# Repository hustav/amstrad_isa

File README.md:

# Amstrad PPC 512/640 — ISA Expansion Board

An open-hardware **KiCad 8** design for an external-mount, internally-powered
**3-slot XT-class (8-bit) ISA expansion board** for the Amstrad PPC 512 and
PPC 640 portable PCs.

The PPC is the 1988-era Amstrad luggable that ships with a CMOS-level
expansion connector (DB25 + DB37) on its back. Amstrad sold an external
"Expansion Box" that was meant to *power* the PPC and add peripheral slots.
This project inverts the original topology: it **takes power from the PPC's
own PSU** and gives you three standard XT 8-bit ISA slots in a compact board
that clips onto the back of the machine via the two DB connectors — ready to
host modern flash-based peripherals (XT-IDE, floppy emulators, network
cards, etc.).

## Gallery

The board has been fabricated and tested in a real Amstrad PPC 640 —
booting DOS from a CompactFlash card via an XT-IDE controller. Photos
below are of the assembled board in service.

| | |
|---|---|
|  |  |
| Board mated to the PPC's DB25 + DB37 expansion port. | Top-down view showing the three ISA slots fanning out the back. |
|  |  |
| XT-IDE card with CompactFlash plugged into the centre slot. | The PPC 640 booting and running Test Drive from the CF card. |

## Repository layout

```
amstrad_isa/
├── README.md                  — this file
├── LICENSE                    — MIT
├── .gitignore                 — KiCad / Python / OS cruft
├── kicad/
│   ├── ppc-isa-expansion.kicad_pro
│   ├── ppc-isa-expansion.kicad_sch
│   ├── ppc-isa-expansion.kicad_pcb
│   ├── sym-lib-table          — project-local symbol libraries
│   ├── fp-lib-table           — project-local footprint libraries
│   └── ppc-isa.pretty/        — custom ISA 8-bit slot footprint
├── scripts/
│   ├── generate_schematic.py  — regenerates the schematic from tables
│   ├── generate_pcb.py        — regenerates the PCB skeleton
│   └── generate_bom.py        — emits docs/BOM.csv
├── fab/                       — ready-to-order gerbers + JLCPCB zip
├── docs/
│   ├── design_notes.md        — the *why* behind the schematic choices
│   ├── BOM.csv                — bill of materials
│   └── Amstrad_PPC_Technical_Reference_Manual.pdf
└── photos/                    — build & in-machine reference shots
```

## I just want a board — no KiCad

If you don't want to install KiCad, the [`fab/`](fab/) folder contains a
ready-to-order gerber set straight from the committed `.kicad_pcb`.

1. Download [`fab/ppc-isa-expansion-gerbers.zip`](fab/ppc-isa-expansion-gerbers.zip)
   (no need to extract it).
2. Go to your favourite board house — **JLCPCB**, **PCBWay**, **OSH Park**
   and **Aisler** all accept this format unchanged.
3. Upload the zip. The defaults are fine: 2 layers, 1.6 mm FR-4, HASL or
   ENIG finish, any colour. Quantity 5 is usually the minimum and runs
   ~$5 + shipping.
4. Order, wait, populate from [`docs/BOM.csv`](docs/BOM.csv).

The gerbers in `fab/` always match the committed `.kicad_pcb`. If you fork
and re-route, re-plot from KiCad and replace the contents of `fab/`.

## Build from source (with KiCad)

```bash
git clone git@github.com:hustav/amstrad_isa.git
cd amstrad_isa

# Optional: regenerate the schematic / PCB from the Python source of truth
python3 scripts/generate_schematic.py
python3 scripts/generate_pcb.py

# Open the project
kicad kicad/ppc-isa-expansion.kicad_pro
```

The `.kicad_sch` and `.kicad_pcb` files were initially **generated** by the
scripts in `scripts/` — those scripts remain the source of truth for the
netlist. The current `.kicad_pcb` has been routed by hand on top of that
skeleton, so re-running `generate_pcb.py` would overwrite the routing.
If you need to change the netlist, regenerate the skeleton and then redo
the affected traces.

## Key design choices

| Area | Choice | Reason |
| --- | --- | --- |
| Form factor | External-mount, ~120 × 99 mm | Clips onto the PPC's DB25 + DB37 expansion port |
| Slots | 3 × XT 8-bit ISA (62-pin) | Standard pinout, matches prior-art boards |
| Power source | Drawn from the PPC's internal PSU via the expansion cable | No external brick required |
| −5 V rail | Taken directly from connector B pin 17 | Tech Ref §1.18 confirms PPC sources −5 V |
| Component style | SMD only — SOIC, 0805, SIP network | Hand-solderable with a fine-tip iron |
| Buffering | 2 × 74HC244 for A00..A07 + 8 control signals | Drives the loaded capacitance of 3 ISA slots |
| Data bus | Unbuffered, 10 kΩ pull-ups via RR1 | Per Amstrad Tech Ref CMOS-to-TTL note |
| Activity LED | Removed (BEAT flip-flop omitted) | Purely cosmetic; saves 1× SOIC-14 + RC bits |

Full rationale lives in [docs/design_notes.md](docs/design_notes.md).

## Power topology — important caveat

The Amstrad PPC Technical Reference Manual (§1.18) states that the original
Expansion Box is intended to *supply* power **to** the PPC, not draw from
it. Connector B pin 20 is an **EXT PWR input** to the PPC's regulator.

This design **reverses that flow** — all four rails (+5 V, +12 V, −5 V,
−12 V) are *drawn* from the PPC's expansion connector:

- +5 V from connector A pin 1 and connector B pin 37
- +12 V from connector B pin 36
- −5 V from connector B pin 17
- −12 V from connector B pin 18

Pin 20 (EXT PWR into the PPC) is **left floating** — voltage is never
injected back into the PPC.

**Safe for modern peripherals.** An original floppy or 10 MB Winchester drew
5–10 W. A flash-based XT-IDE with a CF card draws ~100–200 mA on +5 V
(0.5–1 W). Three flash peripherals are comfortably within the headroom the
original PSU left for the Expansion Box port.

**Not safe for original drives.** If you try to use the original floppy or
HDD controllers through this board, the PPC's PSU may brown out. In that
case, build an externally-powered (ATX) variant instead.

## Amstrad expansion pinout (Tech Ref §1.18)

### Connector A (DB25 male on the board)

Mostly the address bus.

| Pin | Signal | Notes |
| --- | --- | --- |
| 1 | +5 V | **power input** |
| 2 | TC | DMA terminal-count |
| 3, 16, 4, 17, 5, 18, 6, 19, 7, 20, 8, 21 | A19..A08 | Unbuffered |
| 9, 22, 10, 23, 11, 24, 12, 25 | A07b..A00b | Buffered on PPC side; re-buffered by U2 |
| 13 | AEN | Address enable |
| 14 | GND | |
| 15 | DACK0 | |

### Connector B (DB37 male on the board)

Data bus, IRQs, DMA, control signals, power.

| Pin | Signal | Notes |
| --- | --- | --- |
| 1 | −20 V | **unused, left NC** |
| 2–4, 21–23 | IRQ2..IRQ7 | Pass-through |
| 5 | I/O RDY | Pass-through |
| 6, 24–25 | DACK1..DACK3 | Pass-through |
| 7 | I/O CHCK | Pass-through |
| 8, 26–27 | DRQ1..DRQ3 | Pass-through |
| 9 | OSC(b) | 14.318 MHz buffered on PPC side; re-buffered by U1 |
| 10–12, 28–31 | MEMR(b), IOR(b), ALE(b), MEMW(b), IOW(b), RESET(b), CK4(b) | Re-buffered by U1 |
| 13–16, 32–35 | D7..D0 | Unbuffered; 10 kΩ pull-ups via RR1 |
| 17 | −5 V | **power input** |
| 18 | −12 V | **power input** |
| 19 | GND | |
| 20 | EXT PWR | **NOT USED** — would feed the PPC's regulator |
| 36 | +12 V | **power input** |
| 37 | +5 V | **power input** |

The full Amstrad PPC Technical Reference Manual is included in
[docs/](docs/Amstrad_PPC_Technical_Reference_Manual.pdf) for reference.

## Credits and prior art

This design builds on two community projects, both of which are
externally-mounted boards that hang off the PPC's DB25 + DB37 connectors:

- **João (enide.net)** — original internally-powered design. Provided the
  mechanical approach and power topology. Only the gerbers were available
  (the project is currently offline), so the schematic was reverse-
  engineered from those files and cross-referenced against the
  Retrotheory design below.
- **Retrotheory — [amstradppc_expansion](https://github.com/retrotheory/amstradppc_expansion)** —
  ATX-powered variant. Provided the full schematic used as the electrical
  reference (74HC244 pinouts, the BEAT LED divider using a 74HC74, etc.).

Many thanks to both for sharing their work — without them this design
would not exist.

## License

Released under the **MIT License**. See [LICENSE](LICENSE).

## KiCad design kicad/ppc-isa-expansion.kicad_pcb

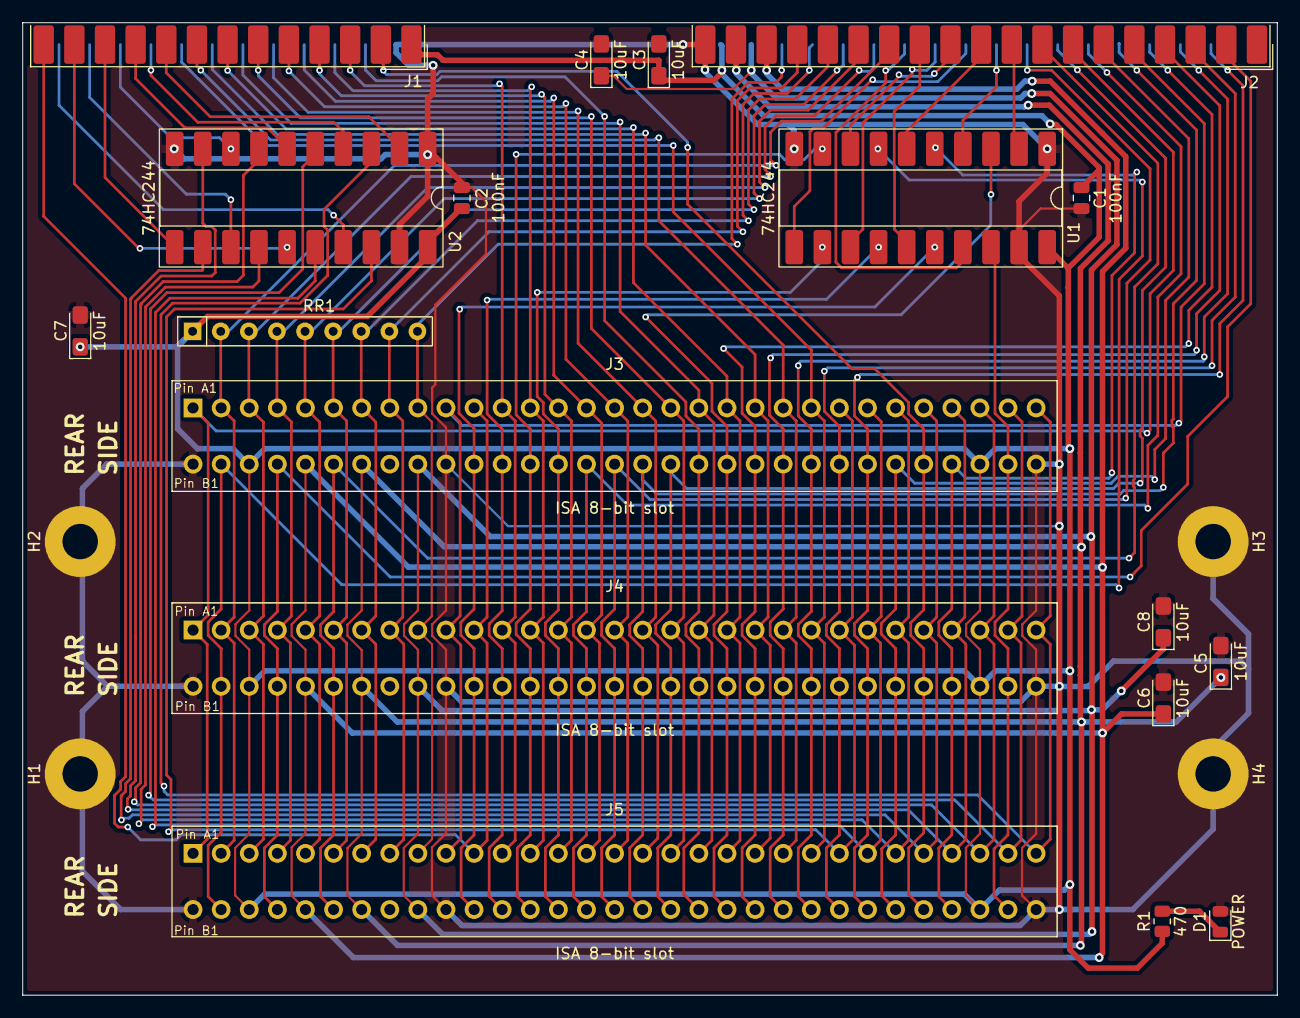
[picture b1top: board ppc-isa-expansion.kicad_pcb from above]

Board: 2 copper layers, 113.4 x 87.9 mm, 22 parts (0 on the bottom side), 75 nets.

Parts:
C1, C2: 100nF; C_0805_2012Metric
C3, C4, C5, C6, C7, C8: 10uF; CP_EIA-3216-12_Kemet-S_HandSolder
D1: POWER; LED_0805_2012Metric
H1, H2, H3, H4: MountingHole_M3; MountingHole_3.2mm_M3_Pad
J1: DB25 Male; DSUB-25_Pins_EdgeMount_P2.77mm
J2: DB37 Male; DSUB-37_Pins_EdgeMount_P2.77mm
J3, J4, J5: ISA 8-bit slot; ISA_8Bit_Slot
R1: 470; R_0805_2012Metric
RR1: 10k; R_Array_SIP9
U1, U2: 74HC244; DIP-20_W8.89mm_SMDSocket_LongPads

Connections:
+5V: C1.1, C2.1, C3.1, C7.1, J1.1 (+5V), J2.37 (+5V), J3.34 (+5V), J3.60 (+5V), J4.34 (+5V), J4.60 (+5V), J5.34 (+5V), J5.60 (+5V), R1.1, RR1.1 (COM), U1.20 (VCC), U2.20 (VCC)
+12V: C4.1, C8.1, J2.36 (+12V), J3.40 (+12V), J4.40 (+12V), J5.40 (+12V)
-5V: C6.1, J2.17 (-5V), J3.36 (-5V), J4.36 (-5V), J5.36 (-5V)
-12V: C5.1, J2.18 (-12V), J3.38 (-12V), J4.38 (-12V), J5.38 (-12V)
A00: J3.31 (A00), J4.31 (A00), J5.31 (A00), U2.3 (2Y3)
A00b: J1.25 (A00b), U2.17 (2A3)
A01: J3.30 (A01), J4.30 (A01), J5.30 (A01), U2.5 (2Y2)
A01b: J1.12 (A01b), U2.15 (2A2)
A02: J3.29 (A02), J4.29 (A02), J5.29 (A02), U2.7 (2Y1)
A02b: J1.24 (A02b), U2.13 (2A1)
A03: J3.28 (A03), J4.28 (A03), J5.28 (A03), U2.9 (2Y0)
A03b: J1.11 (A03b), U2.11 (2A0)
A04: J3.27 (A04), J4.27 (A04), J5.27 (A04), U2.12 (1Y3)
A04b: J1.23 (A04b), U2.8 (1A3)
A05: J3.26 (A05), J4.26 (A05), J5.26 (A05), U2.14 (1Y2)
A05b: J1.10 (A05b), U2.6 (1A2)
A06: J3.25 (A06), J4.25 (A06), J5.25 (A06), U2.16 (1Y1)
A06b: J1.22 (A06b), U2.4 (1A1)
A07: J3.24 (A07), J4.24 (A07), J5.24 (A07), U2.18 (1Y0)
A07b: J1.9 (A07b), U2.2 (1A0)
A08: J1.21 (A08), J3.23 (A08), J4.23 (A08), J5.23 (A08)
A09: J1.8 (A09), J3.22 (A09), J4.22 (A09), J5.22 (A09)
A10: J1.20 (A10), J3.21 (A10), J4.21 (A10), J5.21 (A10)
A11: J1.7 (A11), J3.20 (A11), J4.20 (A11), J5.20 (A11)
A12: J1.19 (A12), J3.19 (A12), J4.19 (A12), J5.19 (A12)
A13: J1.6 (A13), J3.18 (A13), J4.18 (A13), J5.18 (A13)
A14: J1.18 (A14), J3.17 (A14), J4.17 (A14), J5.17 (A14)
A15: J1.5 (A15), J3.16 (A15), J4.16 (A15), J5.16 (A15)
A16: J1.17 (A16), J3.15 (A16), J4.15 (A16), J5.15 (A16)
A17: J1.4 (A17), J3.14 (A17), J4.14 (A17), J5.14 (A17)
A18: J1.16 (A18), J3.13 (A18), J4.13 (A18), J5.13 (A18)
A19: J1.3 (A19), J3.12 (A19), J4.12 (A19), J5.12 (A19)
AEN: J1.13 (AEN), J3.11 (AEN), J4.11 (AEN), J5.11 (AEN)
ALE: J3.59 (ALE), J4.59 (ALE), J5.59 (ALE), U1.5 (2Y2)
ALEb: J2.12 (ALEb), U1.15 (2A2)
CK4b: J2.31 (CK4b), U1.17 (2A3)
CLK: J3.51 (CLK), J4.51 (CLK), J5.51 (CLK), U1.3 (2Y3)
D0: J2.35 (D0), J3.9 (D0), J4.9 (D0), J5.9 (D0), RR1.9 (R8)
D1: J2.16 (D1), J3.8 (D1), J4.8 (D1), J5.8 (D1), RR1.8 (R7)
D2: J2.34 (D2), J3.7 (D2), J4.7 (D2), J5.7 (D2), RR1.7 (R6)
D3: J2.15 (D3), J3.6 (D3), J4.6 (D3), J5.6 (D3), RR1.6 (R5)
D4: J2.33 (D4), J3.5 (D4), J4.5 (D4), J5.5 (D4), RR1.5 (R4)
D5: J2.14 (D5), J3.4 (D5), J4.4 (D5), J5.4 (D5), RR1.4 (R3)
D6: J2.32 (D6), J3.3 (D6), J4.3 (D6), J5.3 (D6), RR1.3 (R2)
D7: J2.13 (D7), J3.2 (D7), J4.2 (D7), J5.2 (D7), RR1.2 (R1)
DRQ1: J2.26 (DRQ1), J3.49 (DRQ1), J4.49 (DRQ1), J5.49 (DRQ1)
DRQ2: J2.8 (DRQ2), J3.37 (DRQ2), J4.37 (DRQ2), J5.37 (DRQ2)
DRQ3: J2.27 (DRQ3), J3.47 (DRQ3), J4.47 (DRQ3), J5.47 (DRQ3)
GND: C1.2, C2.2, C3.2, C4.2, C5.2, C6.2, C7.2, C8.2, D1.2 (A), H1.1, H2.1, H3.1, H4.1, J1.14 (GND), J2.19 (GND), J3.32 (GND), J3.41 (GND), J3.62 (GND), J4.32 (GND), J4.41 (GND), J4.62 (GND), J5.32 (GND), J5.41 (GND), J5.62 (GND), U1.1 (~1OE), U1.10 (GND), U1.19 (~2OE), U2.1 (~1OE), U2.10 (GND), U2.19 (~2OE)
IO_RDY: J2.5 (IO_RDY), J3.10 (IO_RDY), J4.10 (IO_RDY), J5.10 (IO_RDY)
IRQ2: J2.2 (IRQ2), J3.35 (IRQ2), J4.35 (IRQ2), J5.35 (IRQ2)
IRQ3: J2.21 (IRQ3), J3.56 (IRQ3), J4.56 (IRQ3), J5.56 (IRQ3)
IRQ4: J2.3 (IRQ4), J3.55 (IRQ4), J4.55 (IRQ4), J5.55 (IRQ4)
IRQ5: J2.22 (IRQ5), J3.54 (IRQ5), J4.54 (IRQ5), J5.54 (IRQ5)
IRQ6: J2.4 (IRQ6), J3.53 (IRQ6), J4.53 (IRQ6), J5.53 (IRQ6)
IRQ7: J2.23 (IRQ7), J3.52 (IRQ7), J4.52 (IRQ7), J5.52 (IRQ7)
unnamed: D1.1 (K), R1.2
OSC: J3.61 (OSC), J4.61 (OSC), J5.61 (OSC), U1.18 (1Y0)
OSCb: J2.9 (OSCb), U1.2 (1A0)
RESET: J3.33 (RESET), J4.33 (RESET), J5.33 (RESET), U1.7 (2Y1)
RESETb: J2.30 (RESETb), U1.13 (2A1)
TC: J1.2 (TC), J3.58 (TC), J4.58 (TC), J5.58 (TC)
~DACK0: J1.15 (~DACK0), J3.50 (~DACK0), J4.50 (~DACK0), J5.50 (~DACK0)
~DACK1: J2.24 (~DACK1), J3.48 (~DACK1), J4.48 (~DACK1), J5.48 (~DACK1)
~DACK2: J2.6 (~DACK2), J3.57 (~DACK2), J4.57 (~DACK2), J5.57 (~DACK2)
~DACK3: J2.25 (~DACK3), J3.46 (~DACK3), J4.46 (~DACK3), J5.46 (~DACK3)
~IOCHCK: J2.7 (~IOCHCK), J3.1 (~IOCHCK), J4.1 (~IOCHCK), J5.1 (~IOCHCK)
~IOR: J3.45 (~IOR), J4.45 (~IOR), J5.45 (~IOR), U1.12 (1Y3)
~IORb: J2.11 (~IORb), U1.8 (1A3)
~IOW: J3.44 (~IOW), J4.44 (~IOW), J5.44 (~IOW), U1.9 (2Y0)
~IOWb: J2.29 (~IOWb), U1.11 (2A0)
~MEMRb: J2.10 (~MEMRb), U1.6 (1A2)
~MEMWb: J2.28 (~MEMWb), U1.4 (1A1)
~SMEMR: J3.43 (~SMEMR), J4.43 (~SMEMR), J5.43 (~SMEMR), U1.14 (1Y2)
~SMEMW: J3.42 (~SMEMW), J4.42 (~SMEMW), J5.42 (~SMEMW), U1.16 (1Y1)

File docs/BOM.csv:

References,Quantity,Value,Footprint,Description,Notes
"U1, U2",2,74HC244,Package_SO:SOIC-20W_7.5x12.8mm_P1.27mm,"Octal bus buffer / line driver, non-inverting",SOIC-20 wide body; any 74HC244 or 74HCT244 works
"C1, C2, C3, C4, C5",5,100nF,Capacitor_SMD:C_0805_2012Metric,"Chip capacitor, X7R ceramic",0805; 50V rating
"C6, C7, C8, C9",4,10uF,Capacitor_SMD:C_0805_2012Metric,"Chip capacitor, X7R ceramic",0805; 50V rating
J1,1,DB25 Male,Connector_Dsub:DSUB-25_Male_Horizontal_P2.77x2.84mm_EdgePinOffset4.94mm_Housed_MountingHolesOffset7.48mm,"D-sub 25-pin male, right-angle PCB mount",mates with Amstrad Expansion Connector A
J2,1,DB37 Male,Connector_Dsub:DSUB-37_Male_Horizontal_P2.77x2.84mm_EdgePinOffset4.94mm_Housed_MountingHolesOffset7.48mm,"D-sub 37-pin male, right-angle PCB mount",mates with Amstrad Expansion Connector B
"J3, J4, J5",3,ISA 8-bit slot,Connector:ISA_Slot_8bit_2x31_P2.54mm_Vertical,XT 8-bit ISA slot (62-pin card-edge socket),2x31 on 2.54 mm pitch; 5.08 mm between rows
D1_PWR,1,LED_POWER,LED_SMD:LED_0805_2012Metric,Chip LED,0805; choose visible colour (green/red/amber)
R101,1,470,Resistor_SMD:R_0805_2012Metric,Chip resistor,0805 (2012 metric); +/-1% or 5% is fine
RR1,1,10k,Resistor_THT:R_Array_SIP9,9-pin SIP resistor network (8 bussed resistors),10K value; Bourns 4609X-101-103 or equivalent

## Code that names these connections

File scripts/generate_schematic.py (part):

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# Exact mapping will be:
U1_NETS = {
    "1":  "GND",      # ~1OE tied low (always enabled)
    "2":  "OSCb",     # 1A0 in:  from J2 pin 9
    "4":  "~MEMWb",   # 1A1 in:  from J2 pin 28
    "6":  "~MEMRb",   # 1A2 in:  from J2 pin 10
    "8":  "~IORb",    # 1A3 in:  from J2 pin 11
    "11": "~IOWb",    # 2A0 in:  from J2 pin 29
    "13": "RESETb",   # 2A1 in:  from J2 pin 30
    "15": "ALEb",     # 2A2 in:  from J2 pin 12
    "17": "CK4b",     # 2A3 in:  from J2 pin 31
    "18": "OSC",      # 1Y0 out -> ISA OSC (buffered OSCb)
    "16": "~SMEMW",   # 1Y1 out -> ISA ~SMEMW
    "14": "~SMEMR",   # 1Y2 out -> ISA ~SMEMR
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# provides those pull-ups.  Because we use global labels, naming them D0..D7
# on both sides is all that is required — no additional wiring step needed.
#
# The A00b..A07b pins on J1 (DB25) are buffered INPUTS to U2 — they stay
# distinct from unbuffered A00..A07 which go to the ISA slots.
# A08..A19 on J1/J2 are already unbuffered on the Amstrad side and go
# directly to the ISA bus.  Their current net names already match.
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
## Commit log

2026-05-18 Initial commit: KiCad 8 design + docs + photos
2026-05-19 Add fab/ with ready-to-order gerbers
